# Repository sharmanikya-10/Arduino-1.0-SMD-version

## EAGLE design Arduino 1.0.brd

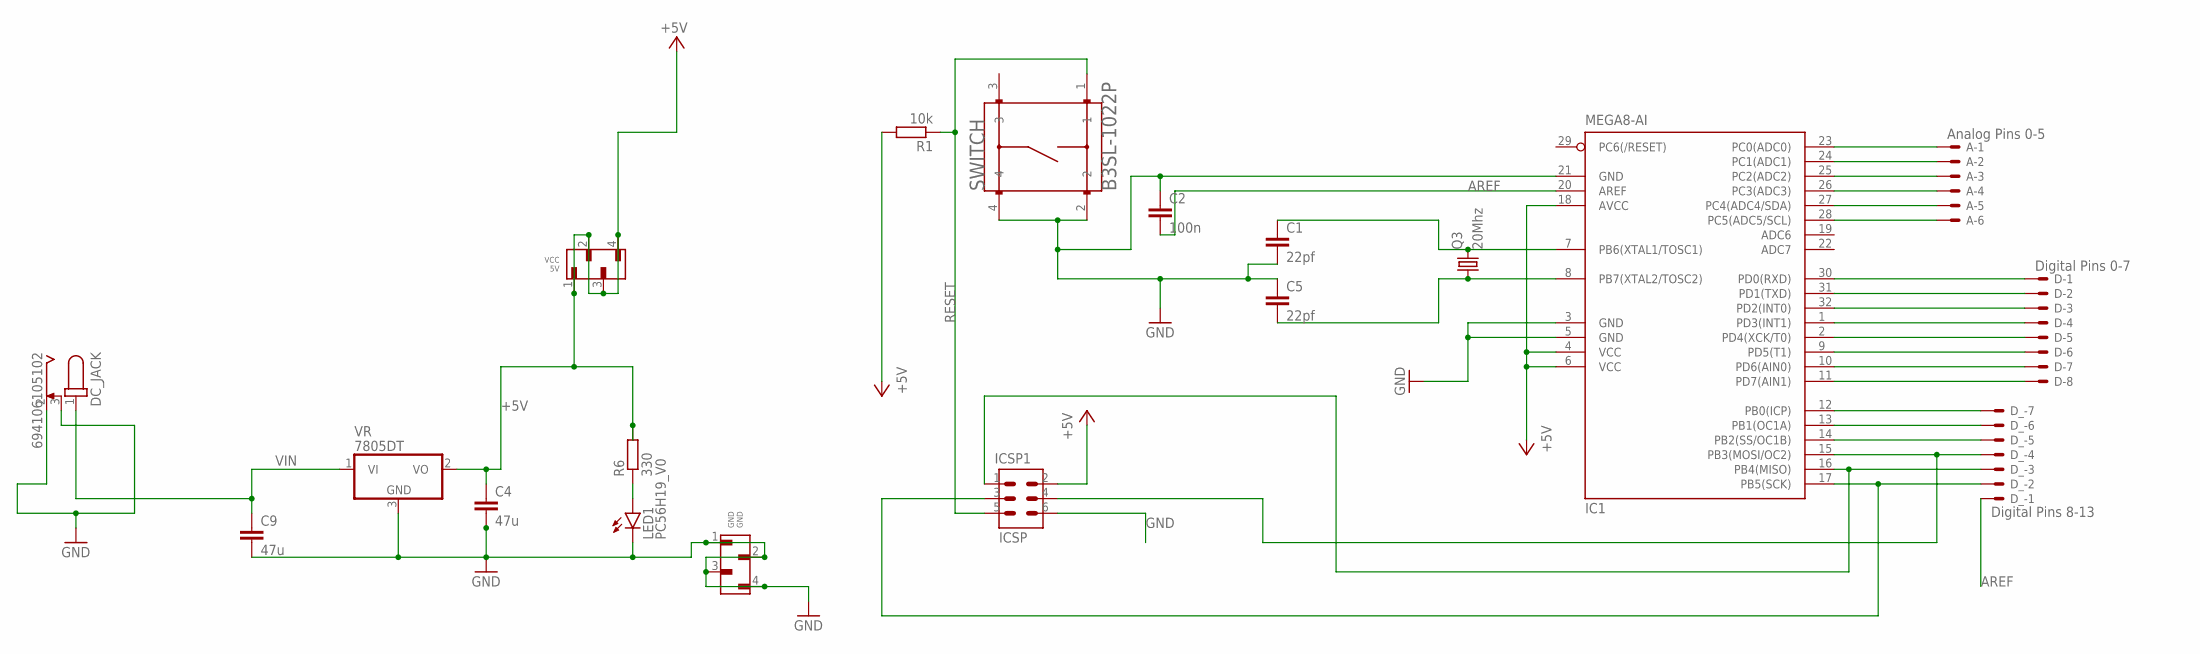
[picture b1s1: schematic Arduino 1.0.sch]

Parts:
A: Analog Pins 0-5; 87438-06
C1, C5: 22pf; C0805
C2: 100n; C0805
C4, C9: 47u; C0805
D: Digital Pins 0-7; 87438-08
DC_JACK: 694106105102
D_: Digital Pins 8-13; 87438-07
GND: GND; 61000418221
IC1: MEGA8-AI; TQFP32-08
ICSP1: ICSP; 621006245821
LED1: PC56H19_V0
Q3: 20Mhz; FC-12M
R1: 10k; M0805
R6: 330; M0805
SWITCH: B3SL-1022P; SW_B3SL-1022P
VCC: 5V; 61000418221
VR: 7805DT; TO252

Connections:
+5V: C4.1, IC1.4 (VCC), IC1.6 (VCC), IC1.18 (AVCC), ICSP1.2, R1.2, R6.2, VCC.1, VCC.2, VCC.3, VCC.4, VR.2 (VO)
AREF: C2.2, D_.1, IC1.20 (AREF)
GND: C1.2, C2.1, C4.2, C5.1, C9.2, DC_JACK.2, DC_JACK.3, GND.1, GND.2, GND.3, GND.4, IC1.3 (GND), IC1.5 (GND), IC1.21 (GND), ICSP1.6, LED1.1 (C), LED1.3 (C), SWITCH.2, SWITCH.4, VR.3 (GND)
unnamed: C1.1, IC1.7 (PB6(XTAL1/TOSC1)), Q3.2
unnamed: D_.2, IC1.17 (PB5(SCK)), ICSP1.3
unnamed: LED1.2 (A), LED1.4 (A), R6.1
unnamed: D_.3, IC1.16 (PB4(MISO)), ICSP1.1
unnamed: C5.2, IC1.8 (PB7(XTAL2/TOSC2)), Q3.1
unnamed: D_.5, IC1.14 (PB2(SS/OC1B))
unnamed: D_.6, IC1.13 (PB1(OC1A))
unnamed: D_.7, IC1.12 (PB0(ICP))
unnamed: D.1, IC1.30 (PD0(RXD))
unnamed: D.2, IC1.31 (PD1(TXD))
unnamed: D.3, IC1.32 (PD2(INT0))
unnamed: D.4, IC1.1 (PD3(INT1))
unnamed: D.5, IC1.2 (PD4(XCK/T0))
unnamed: D.6, IC1.9 (PD5(T1))
unnamed: D.7, IC1.10 (PD6(AIN0))
unnamed: D.8, IC1.11 (PD7(AIN1))
unnamed: A.1, IC1.23 (PC0(ADC0))
unnamed: A.2, IC1.24 (PC1(ADC1))
unnamed: A.3, IC1.25 (PC2(ADC2))
unnamed: A.4, IC1.26 (PC3(ADC3))
unnamed: A.5, IC1.27 (PC4(ADC4/SDA))
unnamed: A.6, IC1.28 (PC5(ADC5/SCL))
unnamed: D_.4, IC1.15 (PB3(MOSI/OC2)), ICSP1.4
RESET: ICSP1.5, R1.1, SWITCH.1
VIN: C9.1, DC_JACK.1, VR.1 (VI)

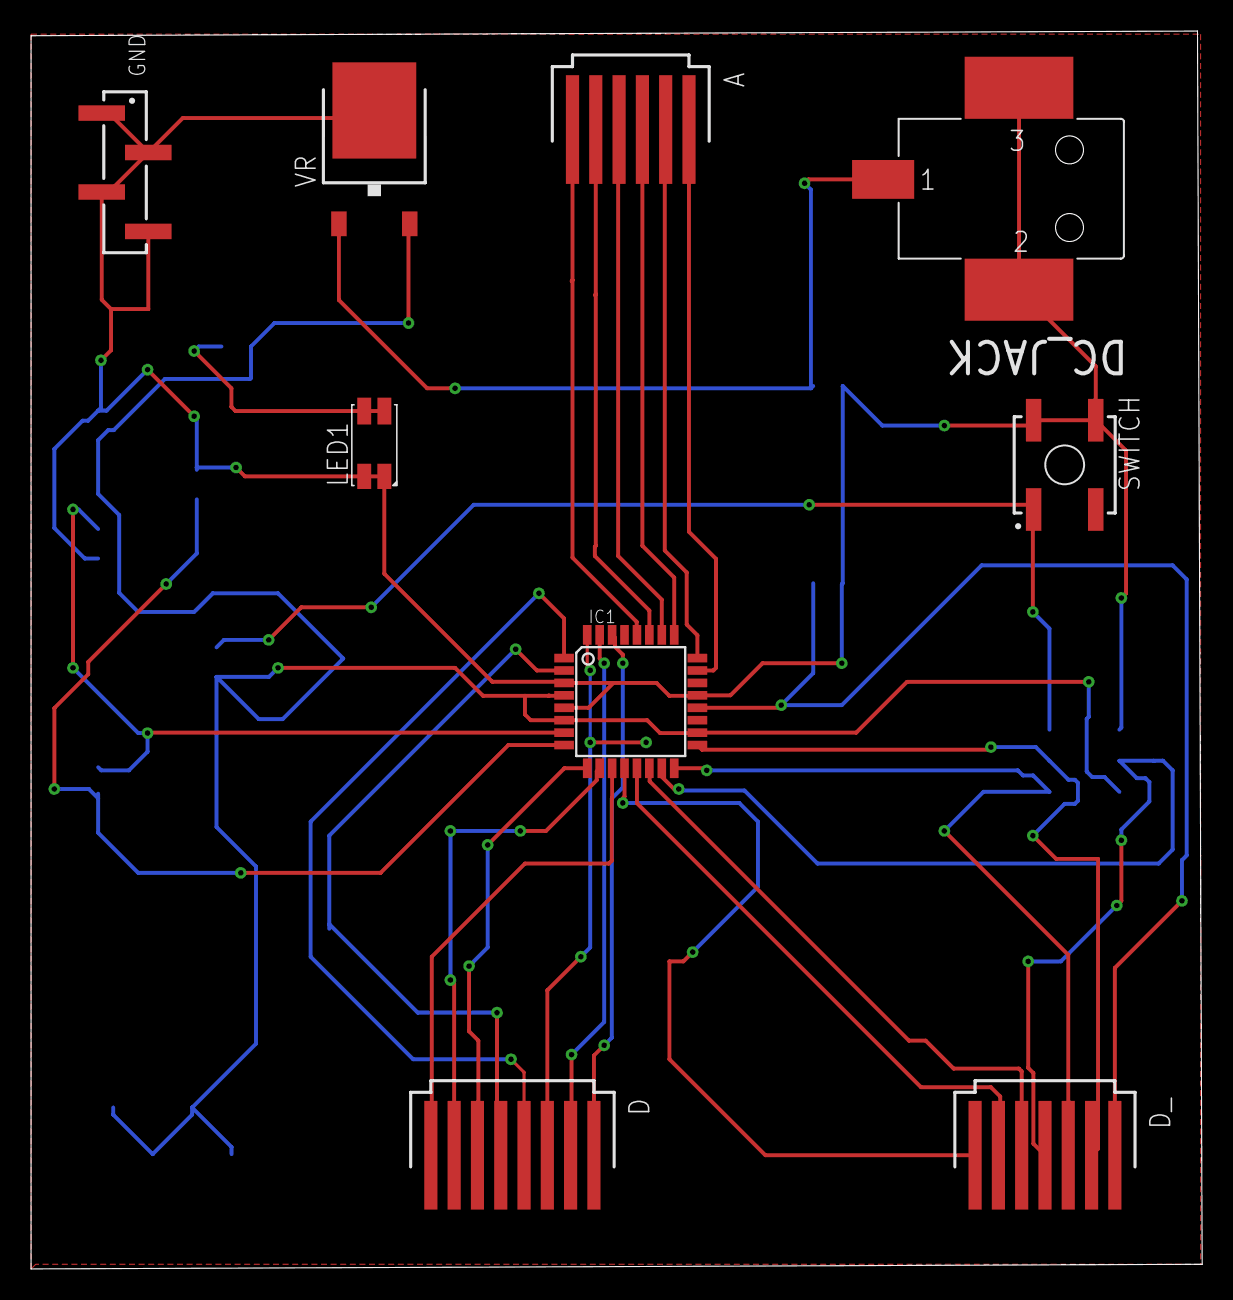
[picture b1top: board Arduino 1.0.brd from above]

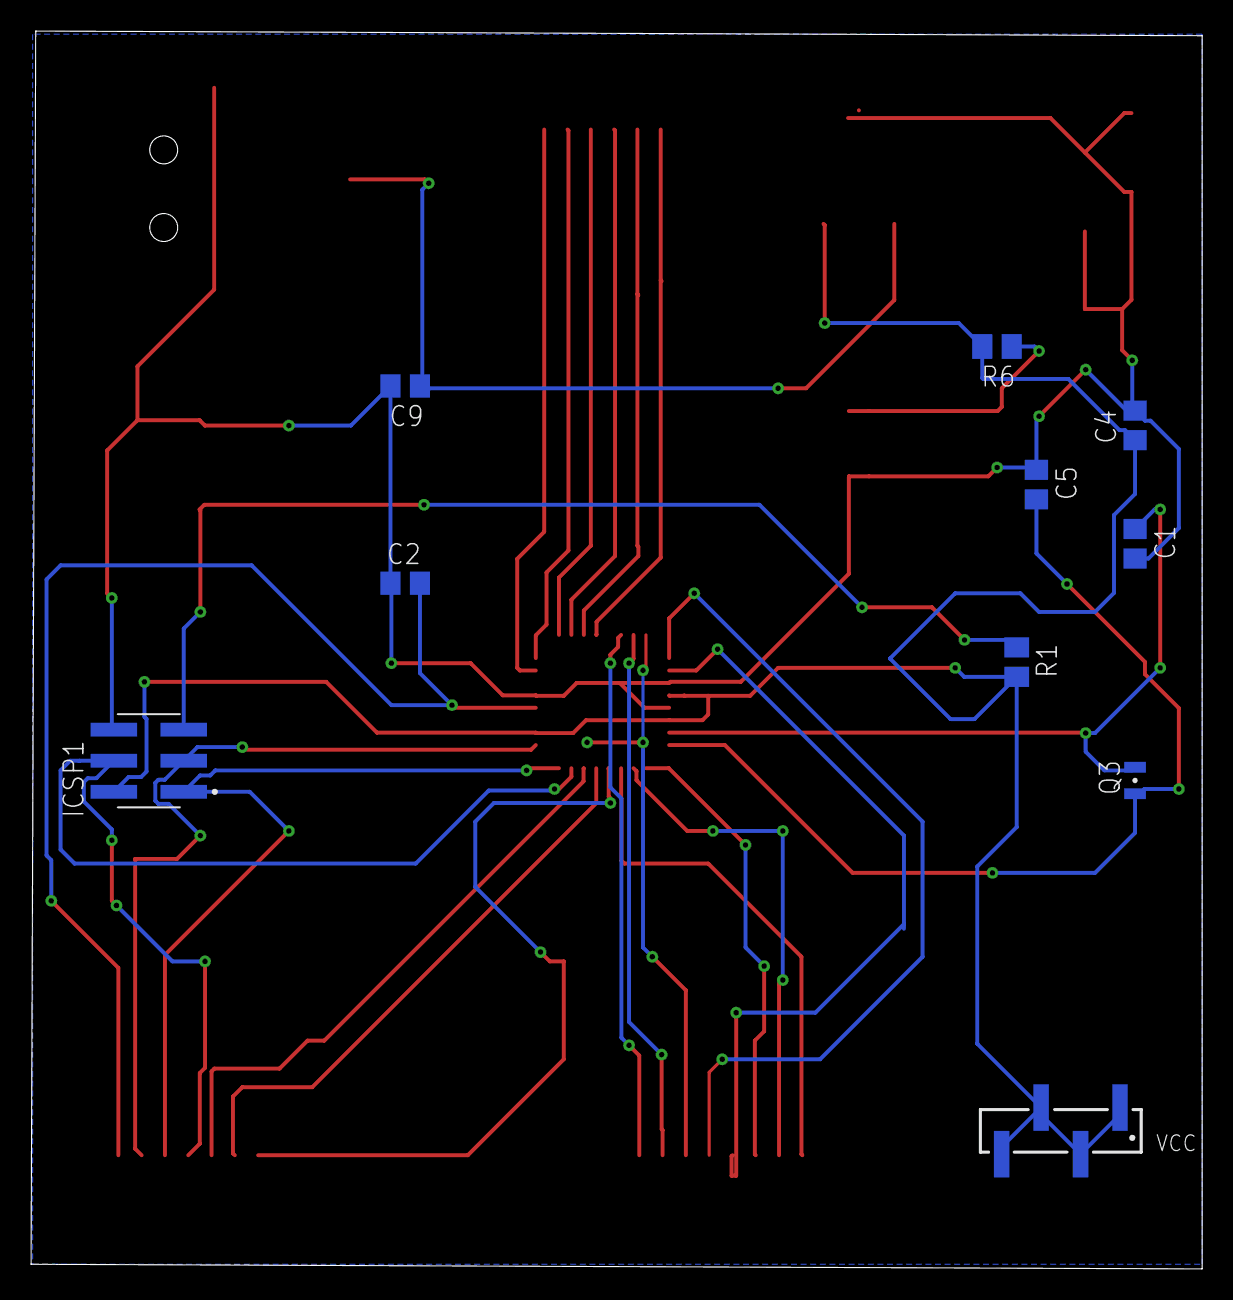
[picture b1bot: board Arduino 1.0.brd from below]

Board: 2 copper layers, 75.4 x 79.7 mm, 19 parts (10 on the bottom side), 28 nets.

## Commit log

2022-09-08 Added Files

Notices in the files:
parts and their libraries:
Wurth_Connectors_WR-PHD: Copyright: Würth Elektronik
